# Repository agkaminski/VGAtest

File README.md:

# VGA test

Proof of concept VGA 640x480@60Hz video adapter. Only 80x60 text mode is
supported, up to 4 fonts (8x8 font, 256 char each.

## PCB

## Example video output

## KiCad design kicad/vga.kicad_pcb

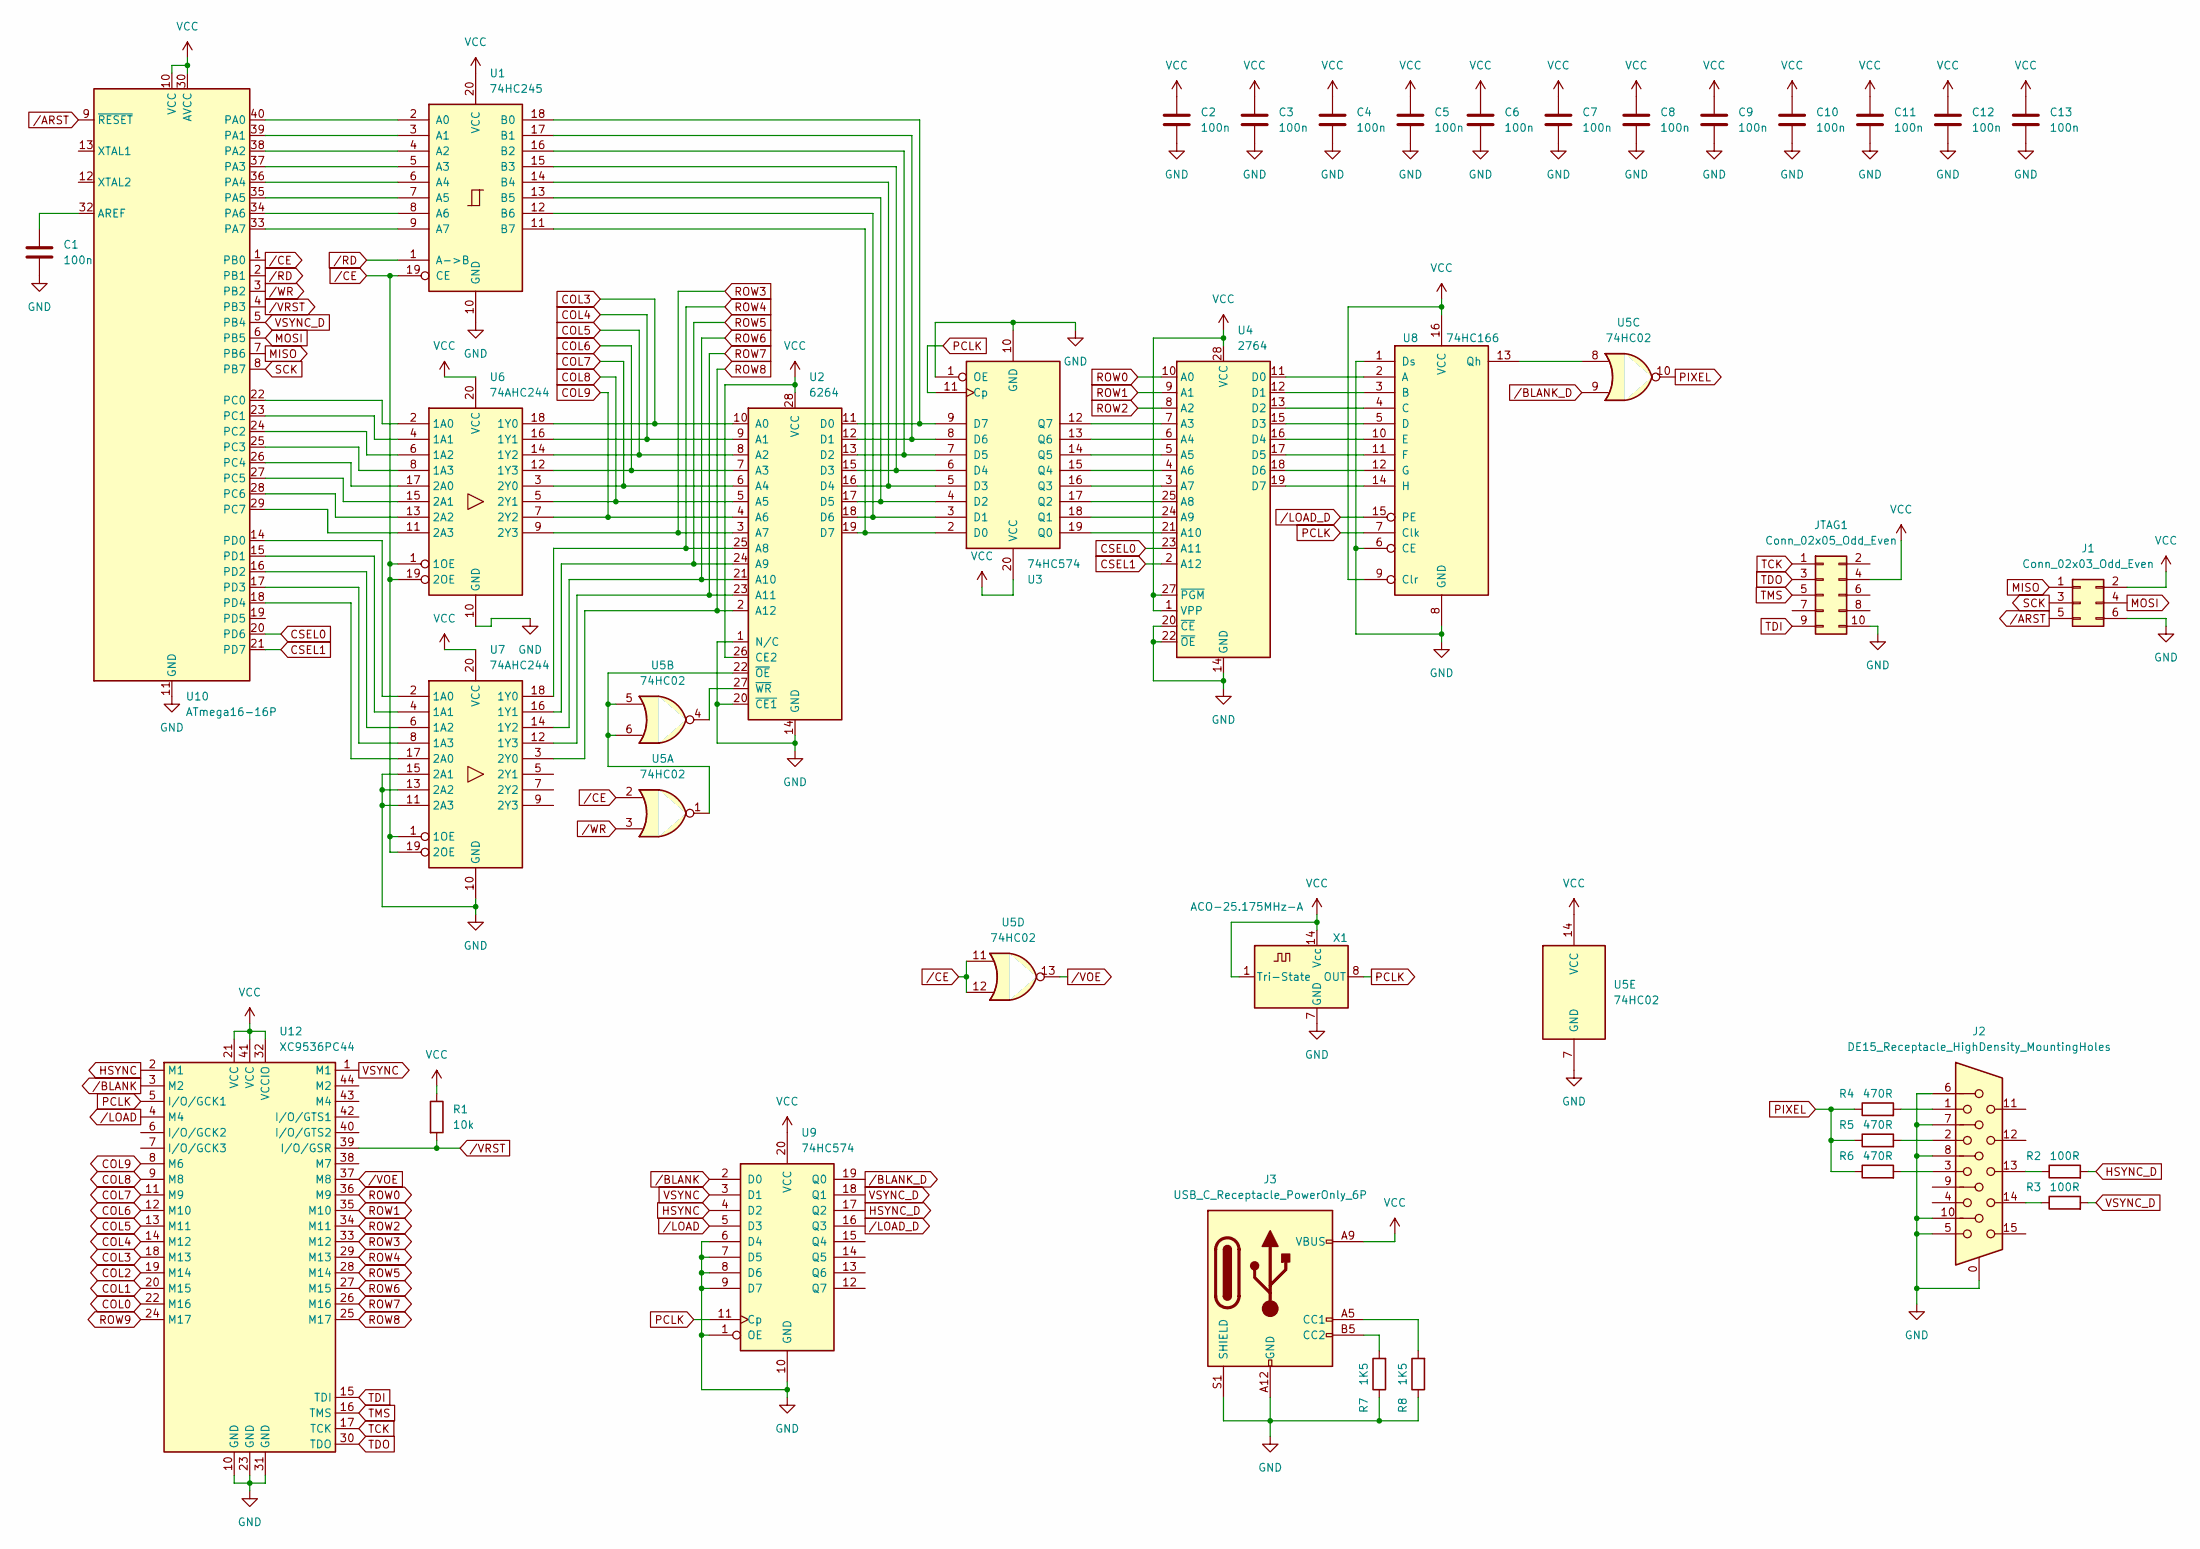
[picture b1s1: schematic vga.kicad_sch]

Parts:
C1, C2, C3, C4, C5, C6, C7, C8, C9, C10, C11, C12, C13: 100n; C_Disc_D5.0mm_W2.5mm_P5.00mm
J1: Conn_02x03_Odd_Even; IDC-Header_2x03_P2.54mm_Vertical
J2: DE15_Receptacle_HighDensity_MountingHoles; DSUB-15-HD_Female_Horizontal_P2.29x1.98mm_EdgePinOffset3.03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
J3: USB_C_Receptacle_PowerOnly_6P; USB_C_Receptacle_GCT_USB4135-GF-A_6P_TopMnt_Horizontal
JTAG1: Conn_02x05_Odd_Even; IDC-Header_2x05_P2.54mm_Vertical
R1: 10k; R_Axial_DIN0207_L6.3mm_D2.5mm_P10.16mm_Horizontal
R2, R3: 100R; R_Axial_DIN0207_L6.3mm_D2.5mm_P10.16mm_Horizontal
R4, R5, R6: 470R; R_Axial_DIN0207_L6.3mm_D2.5mm_P10.16mm_Horizontal
R7, R8: 1K5; R_Axial_DIN0207_L6.3mm_D2.5mm_P10.16mm_Horizontal
U1: 74HC245; DIP-20_W7.62mm
U2: 6264; DIP-28_W15.24mm
U3, U9: 74HC574; DIP-20_W7.62mm
U4: 2764; DIP-28_W15.24mm
U5: 74HC02; DIP-14_W7.62mm
U6, U7: 74AHC244; DIP-20_W7.62mm
U8: 74HC166; DIP-16_W7.62mm
U10: ATmega16-16P; DIP-40_W15.24mm
U12: XC9536PC44; PLCC-44_THT-Socket
X1: ACO-25.175MHz-A; Oscillator_DIP-14

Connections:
COL0: U12.22 (M16)
COL1: U12.20 (M15)
COL2: U12.19 (M14)
COL3: U2.10 (A0), U6.18 (1Y0), U12.18 (M13)
COL4: U2.9 (A1), U6.16 (1Y1), U12.14 (M12)
COL5: U2.8 (A2), U6.14 (1Y2), U12.13 (M11)
COL6: U2.7 (A3), U6.12 (1Y3), U12.12 (M10)
COL7: U2.6 (A4), U6.3 (2Y0), U12.11 (M9)
COL8: U2.5 (A5), U6.5 (2Y1), U12.9 (M8)
COL9: U2.4 (A6), U6.7 (2Y2), U12.8 (M6)
CSEL0: U4.23 (A11), U10.20 (PD6)
CSEL1: U4.2 (A12), U10.21 (PD7)
GND: C1.2, C2.2, C3.2, C4.2, C5.2, C6.2, C7.2, C8.2, C9.2, C10.2, C11.2, C12.2, C13.2, J1.6, J2.0, J2.5, J2.6, J2.7, J2.8, J2.10, J3.A12 (GND), J3.B12 (GND), J3.S1 (SHIELD), JTAG1.10, R7.1, R8.1, U1.10 (GND), U2.1 (N/C), U2.14 (GND), U2.20 (~CE1), U3.1 (OE), U3.10 (GND), U4.14 (GND), U4.20 (~CE), U4.22 (~OE), U5.7 (GND), U6.10 (GND), U7.10 (GND), U7.11 (2A3), U7.13 (2A2), U7.15 (2A1), U8.1 (Ds), U8.6 (CE), U8.8 (GND), U9.1 (OE), U9.6 (D4), U9.7 (D5), U9.8 (D6), U9.9 (D7), U9.10 (GND), U10.11 (GND), U10.31 (GND), U12.10 (GND), U12.23 (GND), U12.31 (GND), X1.7 (GND)
HSYNC: U9.4 (D2), U12.2 (M1)
HSYNC_D: R2.2, U9.17 (Q2)
MISO: J1.1, U10.7 (PB6)
MOSI: J1.4, U10.6 (PB5)
unnamed: J2.1, R4.2
unnamed: J2.2, R5.2
unnamed: J2.3, R6.2
unnamed: J2.13, R2.1
unnamed: J2.14, R3.1
unnamed: J3.A5 (CC1), R8.2
unnamed: J3.B5 (CC2), R7.2
unnamed: U1.2 (A0), U10.40 (PA0)
unnamed: U1.3 (A1), U10.39 (PA1)
unnamed: U1.4 (A2), U10.38 (PA2)
unnamed: U1.5 (A3), U10.37 (PA3)
unnamed: U1.6 (A4), U10.36 (PA4)
unnamed: U1.7 (A5), U10.35 (PA5)
unnamed: U1.8 (A6), U10.34 (PA6)
unnamed: U1.9 (A7), U10.33 (PA7)
unnamed: U1.18 (B0), U2.11 (D0), U3.9 (D7)
unnamed: U1.17 (B1), U2.12 (D1), U3.8 (D6)
unnamed: U1.16 (B2), U2.13 (D2), U3.7 (D5)
unnamed: U1.15 (B3), U2.15 (D3), U3.6 (D4)
unnamed: U1.14 (B4), U2.16 (D4), U3.5 (D3)
unnamed: U1.13 (B5), U2.17 (D5), U3.4 (D2)
unnamed: U1.12 (B6), U2.18 (D6), U3.3 (D1)
unnamed: U1.11 (B7), U2.19 (D7), U3.2 (D0)
unnamed: U2.22 (~OE), U5.1, U5.5, U5.6
unnamed: U2.27 (~WR), U5.4
unnamed: U3.19 (Q0), U4.21 (A10)
unnamed: U3.18 (Q1), U4.24 (A9)
unnamed: U3.17 (Q2), U4.25 (A8)
unnamed: U3.16 (Q3), U4.3 (A7)
unnamed: U3.15 (Q4), U4.4 (A6)
unnamed: U3.14 (Q5), U4.5 (A5)
unnamed: U3.13 (Q6), U4.6 (A4)
unnamed: U3.12 (Q7), U4.7 (A3)
unnamed: U4.11 (D0), U8.2 (A)
unnamed: U4.12 (D1), U8.3 (B)
unnamed: U4.13 (D2), U8.4 (C)
unnamed: U4.15 (D3), U8.5 (D)
unnamed: U4.16 (D4), U8.10 (E)
unnamed: U4.17 (D5), U8.11 (F)
unnamed: U4.18 (D6), U8.12 (G)
unnamed: U4.19 (D7), U8.14 (H)
unnamed: U5.8, U8.13 (Qh)
unnamed: C1.1, U10.32 (AREF)
unnamed: U6.2 (1A0), U10.22 (PC0)
unnamed: U6.4 (1A1), U10.23 (PC1)
unnamed: U6.6 (1A2), U10.24 (PC2)
unnamed: U6.8 (1A3), U10.25 (PC3)
unnamed: U6.17 (2A0), U10.26 (PC4)
unnamed: U6.15 (2A1), U10.27 (PC5)
unnamed: U6.13 (2A2), U10.28 (PC6)
unnamed: U6.11 (2A3), U10.29 (PC7)
unnamed: U7.2 (1A0), U10.14 (PD0)
unnamed: U7.4 (1A1), U10.15 (PD1)
unnamed: U7.6 (1A2), U10.16 (PD2)
unnamed: U7.8 (1A3), U10.17 (PD3)
unnamed: U7.17 (2A0), U10.18 (PD4)
PCLK: U3.11 (Cp), U8.7 (Clk), U9.11 (Cp), U12.5 (I/O/GCK1), X1.8 (OUT)
PIXEL: R4.1, R5.1, R6.1, U5.10
ROW0: U4.10 (A0), U12.36 (M9)
ROW1: U4.9 (A1), U12.35 (M10)
ROW2: U4.8 (A2), U12.34 (M11)
ROW3: U2.3 (A7), U6.9 (2Y3), U12.33 (M12)
ROW4: U2.25 (A8), U7.18 (1Y0), U12.29 (M13)
ROW5: U2.24 (A9), U7.16 (1Y1), U12.28 (M14)
ROW6: U2.21 (A10), U7.14 (1Y2), U12.27 (M15)
ROW7: U2.23 (A11), U7.12 (1Y3), U12.26 (M16)
ROW8: U2.2 (A12), U7.3 (2Y0), U12.25 (M17)
ROW9: U12.24 (M17)
SCK: J1.3, U10.8 (PB7)
TCK: JTAG1.1, U12.17 (TCK)
TDI: JTAG1.9, U12.15 (TDI)
TDO: JTAG1.3, U12.30 (TDO)
TMS: JTAG1.5, U12.16 (TMS)
VCC: C2.1, C3.1, C4.1, C5.1, C6.1, C7.1, C8.1, C9.1, C10.1, C11.1, C12.1, C13.1, J1.2, J3.A9 (VBUS), J3.B9 (VBUS), JTAG1.4, R1.1, U1.20 (VCC), U2.26 (CE2), U2.28 (VCC), U3.20 (VCC), U4.1 (VPP), U4.27 (~PGM), U4.28 (VCC), U5.14 (VCC), U6.20 (VCC), U7.20 (VCC), U8.9 (Clr), U8.16 (VCC), U9.20 (VCC), U10.10 (VCC), U10.30 (AVCC), U12.21 (VCC), U12.32 (VCCIO), U12.41 (VCC), X1.1 (Tri-State), X1.14 (Vcc)
VSYNC: U9.3 (D1), U12.1 (M1)
VSYNC_D: R3.2, U9.18 (Q1), U10.5 (PB4)
/ARST: J1.5, U10.9 (~RESET)
/BLANK: U9.2 (D0), U12.3 (M2)
/BLANK_D: U5.9, U9.19 (Q0)
/CE: U1.19 (CE), U5.2, U5.11, U5.12, U6.1 (1OE), U6.19 (2OE), U7.1 (1OE), U7.19 (2OE), U10.1 (PB0)
/LOAD: U9.5 (D3), U12.4 (M4)
/LOAD_D: U8.15 (PE), U9.16 (Q3)
/RD: U1.1 (A->B), U10.2 (PB1)
/VOE: U5.13, U12.37 (M8)
/VRST: R1.2, U10.4 (PB3), U12.39 (I/O/GSR)
/WR: U5.3, U10.3 (PB2)

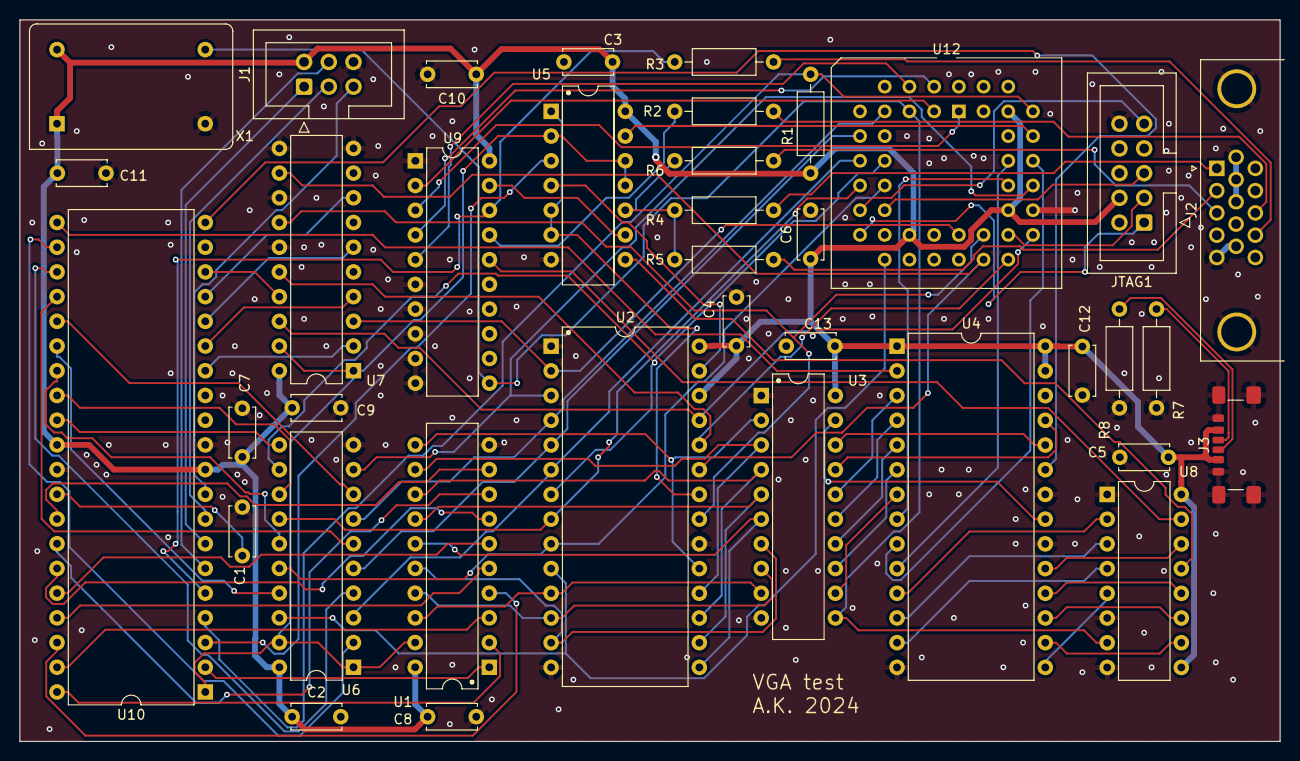
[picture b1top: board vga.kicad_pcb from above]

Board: 2 copper layers, 129.5 x 74.2 mm, 37 parts (0 on the bottom side), 99 nets.

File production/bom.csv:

Designator,Footprint,Quantity,Value,LCSC Part #
"C1, C10, C11, C12, C13, C2, C3, C4, C5, C6, C7, C8, C9",C_Disc_D5.0mm_W2.5mm_P5.00mm,13,100n,
J1,IDC-Header_2x03_P2.54mm_Vertical,1,Conn_02x03_Odd_Even,
J2,DSUB-15-HD_Female_Horizontal_P2.29x1.98mm_EdgePinOffset3.03mm_Housed_MountingHolesOffset4.94mm,1,DE15_Receptacle_HighDensity_MountingHoles,
J3,USB_C_Receptacle_GCT_USB4135-GF-A_6P_TopMnt_Horizontal,1,USB_C_Receptacle_PowerOnly_6P,
JTAG1,IDC-Header_2x05_P2.54mm_Vertical,1,Conn_02x05_Odd_Even,
R1,R_Axial_DIN0207_L6.3mm_D2.5mm_P10.16mm_Horizontal,1,10k,
"R2, R3",R_Axial_DIN0207_L6.3mm_D2.5mm_P10.16mm_Horizontal,2,100R,
"R4, R5, R6",R_Axial_DIN0207_L6.3mm_D2.5mm_P10.16mm_Horizontal,3,470R,
"R7, R8",R_Axial_DIN0207_L6.3mm_D2.5mm_P10.16mm_Horizontal,2,1K5,
U1,DIP-20_W7.62mm,1,74HC245,
U10,DIP-40_W15.24mm,1,ATmega16-16P,
U12,PLCC-44_THT-Socket,1,XC9536PC44,
U2,DIP-28_W15.24mm,1,6264,
"U3, U9",DIP-20_W7.62mm,2,74HC574,
U4,DIP-28_W15.24mm,1,2764,
U5,DIP-14_W7.62mm,1,74HC02,
"U6, U7",DIP-20_W7.62mm,2,74AHC244,
U8,DIP-16_W7.62mm,1,74HC166,
X1,Oscillator_DIP-14,1,ACO-25.175MHz-A,

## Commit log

2024-03-17 Initial import
2024-03-17 Add README and images
